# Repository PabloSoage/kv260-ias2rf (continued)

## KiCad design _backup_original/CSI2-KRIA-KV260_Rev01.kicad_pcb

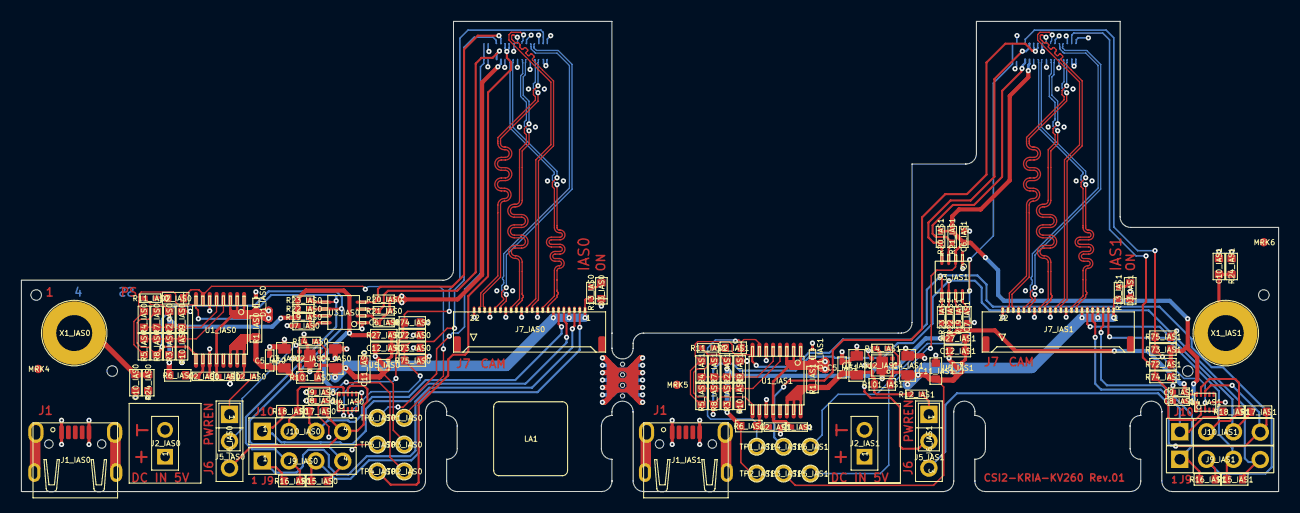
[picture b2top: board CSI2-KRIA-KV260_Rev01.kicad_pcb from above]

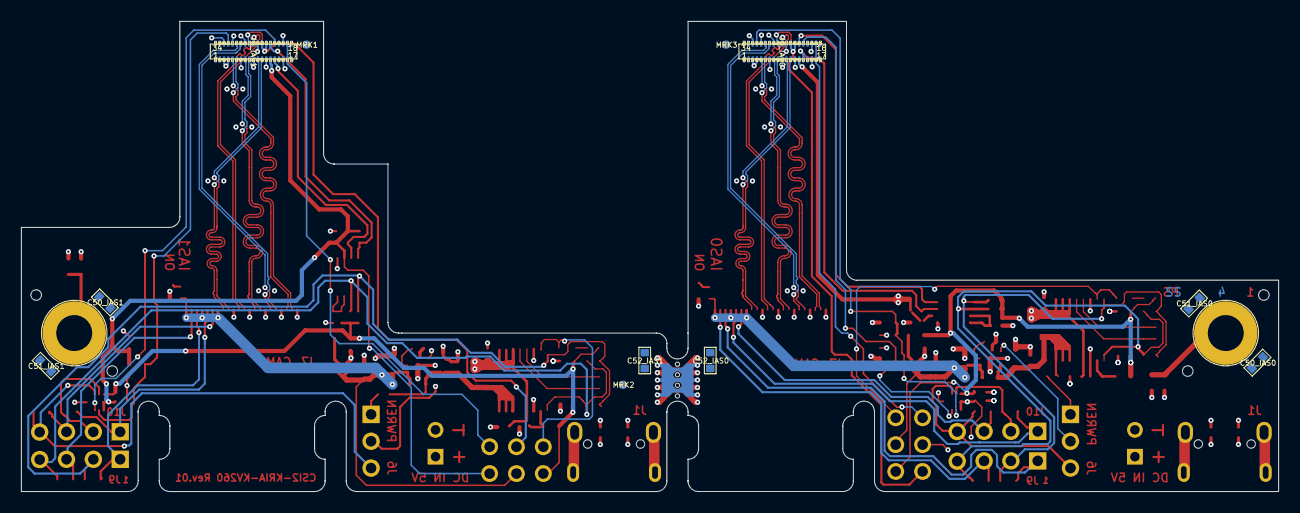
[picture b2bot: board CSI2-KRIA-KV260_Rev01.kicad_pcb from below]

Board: 4 copper layers, 119.0 x 44.5 mm, 145 parts (12 on the bottom side), 82 nets.

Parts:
C1_IAS0, C1_IAS1, C2_IAS0, C2_IAS1: NL; C-0402_0.55
C3_IAS0, C3_IAS1, C4_IAS0, C4_IAS1: 10u; C-0805_1.4
C5_IAS0, C5_IAS1, C6_IAS0, C6_IAS1, C8_IAS0, C8_IAS1, C9_IAS0, C9_IAS1: 100n; C-0402_0.55
C7_IAS0, C7_IAS1: 100p; C-0402_0.55
C10_IAS0, C10_IAS1: NL; C-0603_1.0
C11_IAS0, C11_IAS1, C12_IAS0, C12_IAS1, C50_IAS0, C50_IAS1, C51_IAS0, C51_IAS1, C52_IAS0, C52_IAS1: 4u7; C-0603_1.0
D1_IAS0, D1_IAS1: ESD9B5.0ST5G; D-SOD923
D2_IAS0, D2_IAS1: RED; D-0603-LED
D3_IAS0, D3_IAS1: GREEN; D-0603-LED
J1_IAS0, J1_IAS1: USB 2.0 Typ B 90°; J-629105150521
J2_IAS0, J2_IAS1: CON1x2; CON 1x2 RM2.54
J5_IAS0, J5_IAS1: Jumper; J-JUMPER-2.54
J6_IAS0, J6_IAS1: CON1x3; CON 1x3 RM2.54
J7_IAS0, J7_IAS1: CON FFC22_Inverted; J-FH55-22S-0.5SH - Inverted Pins
J8_IAS0, J8_IAS1: BM20B(0.8)-34DP-0.4V(51); J-BM20B(0.8)-34DP
J9_IAS0, J9_IAS1, J10_IAS0, J10_IAS1: CON1x4; CON 1x4 RM2.54
LA1: LABEL 7x7mm; PCB LABEL 7x7
MRK1, MRK2, MRK3: Marker Single Layer; PCB_Marker_Pad_top
MRK4, MRK5, MRK6: Marker Single Layer; PCB_MARKER_PAD_TOP
R1_IAS0, R1_IAS1, R3_IAS0, R3_IAS1, R9_IAS0, R9_IAS1, R15_IAS0, R15_IAS1, R16_IAS0, R16_IAS1, R24_IAS0, R24_IAS1, R27_IAS0, R27_IAS1: 0R0; R-0603_0.6
R2_IAS0, R2_IAS1, R4_IAS0, R4_IAS1, R5_IAS0, R5_IAS1, R6_IAS0, R6_IAS1, R7_IAS0, R7_IAS1, R8_IAS0, R8_IAS1, R10_IAS0, R10_IAS1, R17_IAS0, R17_IAS1, R18_IAS0, R18_IAS1, R72_IAS0, R72_IAS1, R73_IAS0, R73_IAS1, R74_IAS0, R74_IAS1, R75_IAS0, R75_IAS1, R101_IAS0, R101_IAS1: NL; R-0603_0.6
R11_IAS0, R11_IAS1: NL; R-0402_0.4
R12_IAS0: 270k; R-0402_0.4
R12_IAS1: 270K; R-0402_0.4
R13_IAS0, R13_IAS1: 3k3; R-0402_0.4
R14_IAS0, R14_IAS1: 51k; R-0402_0.4
R19_IAS0, R19_IAS1: 200k; R-0402_0.4
R20_IAS0, R20_IAS1, R21_IAS0, R21_IAS1, R22_IAS0, R22_IAS1, R23_IAS0, R23_IAS1: 2k0; R-0402_0.4
T1: PCB Text TOP; PCB TEXTFIELD TOP 2
T2: PCB Text BOT; PCB TEXTFIELD BOT 2
TP1_IAS0, TP1_IAS1, TP2_IAS0, TP2_IAS1, TP3_IAS0, TP3_IAS1, TP4_IAS0, TP4_IAS1, TP5_IAS0, TP5_IAS1, TP6_IAS0, TP6_IAS1: TP; TP_16_10
U1_IAS0, U1_IAS1: INA260AIPWR; IC-TSSOP16 6.4x5.1x1.2
U2_IAS0, U2_IAS1: TPS25200DRVT; IC-DFN06_2.0x2.0x0.8
U3_IAS0, U3_IAS1: PCA9306DCTR; IC-TSSOP8_3.15x4.25x1.3
U4_IAS0, U4_IAS1: NTB0104GU12,115; IC-XQFN12_1.7x2x0.5
U5_IAS0, U5_IAS1: NCP114AMX330TCG; IC-XDFN4_1.0x1.0x0.6
X1_IAS0, X1_IAS1: Hole; HOLE-3.4-6.0-DK

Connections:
B7-CSI2-TXC_IAS0_N: J7_IAS0.14, J8_IAS0.8
B7-CSI2-TXC_IAS0_P: J7_IAS0.15, J8_IAS0.7
B7-CSI2-TXC_IAS1_N: J7_IAS1.14, J8_IAS1.8
B7-CSI2-TXC_IAS1_P: J7_IAS1.15, J8_IAS1.7
B7-CSI2-TXD0_IAS0_N: J7_IAS0.20, J8_IAS0.5
B7-CSI2-TXD0_IAS0_P: J7_IAS0.21, J8_IAS0.4
B7-CSI2-TXD0_IAS1_N: J7_IAS1.20, J8_IAS1.5
B7-CSI2-TXD0_IAS1_P: J7_IAS1.21, J8_IAS1.4
B7-CSI2-TXD1_IAS0_N: J7_IAS0.17, J8_IAS0.29
B7-CSI2-TXD1_IAS0_P: J7_IAS0.18, J8_IAS0.30
B7-CSI2-TXD1_IAS1_N: J7_IAS1.17, J8_IAS1.29
B7-CSI2-TXD1_IAS1_P: J7_IAS1.18, J8_IAS1.30
B7-CSI2-TXD2_IAS0_N: J7_IAS0.11, J8_IAS0.26
B7-CSI2-TXD2_IAS0_P: J7_IAS0.12, J8_IAS0.27
B7-CSI2-TXD2_IAS1_N: J7_IAS1.11, J8_IAS1.26
B7-CSI2-TXD2_IAS1_P: J7_IAS1.12, J8_IAS1.27
B7-CSI2-TXD3_IAS0_N: J7_IAS0.8, J8_IAS0.11
B7-CSI2-TXD3_IAS0_P: J7_IAS0.9, J8_IAS0.10
B7-CSI2-TXD3_IAS1_N: J7_IAS1.8, J8_IAS1.11
B7-CSI2-TXD3_IAS1_P: J7_IAS1.9, J8_IAS1.10
C-GND_IAS0: C10_IAS0.2, J1_IAS0.6, J1_IAS0.7, J1_IAS0.8, J1_IAS0.9, R24_IAS0.1, X1_IAS0.1
C-GND_IAS1: C10_IAS1.2, J1_IAS1.6, J1_IAS1.7, J1_IAS1.8, J1_IAS1.9, R24_IAS1.1, X1_IAS1.1
EXT-GPIO0-I2C-SCL_IAS0: J7_IAS0.2, J9_IAS0.3, R15_IAS0.1
EXT-GPIO0-I2C-SCL_IAS1: J7_IAS1.2, J9_IAS1.3, R15_IAS1.1
EXT-GPIO1-I2C-SDA_IAS0: J7_IAS0.3, J9_IAS0.1, R16_IAS0.1
EXT-GPIO1-I2C-SDA_IAS1: J7_IAS1.3, J9_IAS1.1, R16_IAS1.1
EXT-GPIO2_IAS0: J7_IAS0.5, J10_IAS0.1, R18_IAS0.1
EXT-GPIO2_IAS1: J7_IAS1.5, J10_IAS1.1, R18_IAS1.1
EXT-GPIO3_IAS0: J7_IAS0.6, J10_IAS0.3, R17_IAS0.1
EXT-GPIO3_IAS1: J7_IAS1.6, J10_IAS1.3, R17_IAS1.1
GND: C1_IAS0.2, C1_IAS1.2, C2_IAS0.2, C2_IAS1.2, C3_IAS0.2, C3_IAS1.2, C4_IAS0.2, C4_IAS1.2, C5_IAS0.2, C5_IAS1.2, C6_IAS0.2, C6_IAS1.2, C7_IAS0.2, C7_IAS1.2, C8_IAS0.2, C8_IAS1.2, C9_IAS0.2, C9_IAS1.2, C10_IAS0.1, C10_IAS1.1, C11_IAS0.2, C11_IAS1.2, C12_IAS0.2, C12_IAS1.2, D1_IAS0.A, D1_IAS1.A, D3_IAS0.K, D3_IAS1.K, J1_IAS0.5, J1_IAS1.5, J2_IAS0.2, J2_IAS1.2, J7_IAS0.10, J7_IAS0.13, J7_IAS0.16, J7_IAS0.19, J7_IAS0.22, J7_IAS1.10, J7_IAS1.13, J7_IAS1.16, J7_IAS1.19, J7_IAS1.22, J8_IAS0.2, J8_IAS0.3, J8_IAS0.6, J8_IAS0.9, J8_IAS0.12, J8_IAS0.16, J8_IAS0.19, J8_IAS0.25, J8_IAS0.28, J8_IAS0.31, J8_IAS0.33, J8_IAS1.2, J8_IAS1.3, J8_IAS1.6, J8_IAS1.9, J8_IAS1.12, J8_IAS1.16, J8_IAS1.19, J8_IAS1.25, J8_IAS1.28, J8_IAS1.31, J8_IAS1.33, R9_IAS0.1, R9_IAS1.1, R10_IAS0.1, R10_IAS1.1, R14_IAS0.1, R14_IAS1.1, R24_IAS0.2, R24_IAS1.2, R74_IAS0.1, R74_IAS1.1, R75_IAS0.1, R75_IAS1.1, U1_IAS0.6, U1_IAS0.11, U1_IAS1.6, U1_IAS1.11, U2_IAS0.5, U2_IAS0.7, U2_IAS1.5, U2_IAS1.7, U3_IAS0.1, U3_IAS1.1, U4_IAS0.6, U4_IAS1.6, U5_IAS0.2, U5_IAS0.5, U5_IAS1.2, U5_IAS1.5
GPIO2_3V3_IAS0: J10_IAS0.2, R18_IAS0.2, U4_IAS0.10
GPIO2_3V3_IAS1: J10_IAS1.2, R18_IAS1.2, U4_IAS1.10
GPIO2_IAS0: J8_IAS0.32, R72_IAS0.1, R74_IAS0.2, U4_IAS0.2
GPIO2_IAS1: J8_IAS1.32, R72_IAS1.1, R74_IAS1.2, U4_IAS1.2
GPIO3_3V3_IAS0: J6_IAS0.3, J10_IAS0.4, R17_IAS0.2, U4_IAS0.9
GPIO3_3V3_IAS1: J6_IAS1.3, J10_IAS1.4, R17_IAS1.2, U4_IAS1.9
I2C_SCL_3V3_IAS0: J9_IAS0.4, R7_IAS0.1, R8_IAS0.1, R15_IAS0.2, R22_IAS0.1, U1_IAS0.9, U3_IAS0.6
I2C_SCL_3V3_IAS1: J9_IAS1.4, R7_IAS1.1, R8_IAS1.1, R15_IAS1.2, R22_IAS1.1, U1_IAS1.9, U3_IAS1.6
I2C_SCL_IAS0: J8_IAS0.14, R21_IAS0.2, U3_IAS0.3
I2C_SCL_IAS1: J8_IAS1.14, R21_IAS1.2, U3_IAS1.3
I2C_SDA_3V3_IAS0: J9_IAS0.2, R4_IAS0.1, R5_IAS0.1, R16_IAS0.2, R23_IAS0.1, U1_IAS0.8, U3_IAS0.5
I2C_SDA_3V3_IAS1: J9_IAS1.2, R4_IAS1.1, R5_IAS1.1, R16_IAS1.2, R23_IAS1.1, U1_IAS1.8, U3_IAS1.5
I2C_SDA_IAS0: J8_IAS0.22, R20_IAS0.2, U3_IAS0.4
I2C_SDA_IAS1: J8_IAS1.22, R20_IAS1.2, U3_IAS1.4
INA260-A0_IAS0: R2_IAS0.2, R4_IAS0.2, R7_IAS0.2, R9_IAS0.2, U1_IAS0.5
INA260-A0_IAS1: R2_IAS1.2, R4_IAS1.2, R7_IAS1.2, R9_IAS1.2, U1_IAS1.5
INA260-A1_IAS0: R3_IAS0.2, R5_IAS0.2, R8_IAS0.2, R10_IAS0.2, U1_IAS0.4
INA260-A1_IAS1: R3_IAS1.2, R5_IAS1.2, R8_IAS1.2, R10_IAS1.2, U1_IAS1.4
NetC2_IAS0_1: C2_IAS0.1, R6_IAS0.2, U1_IAS0.10
NetC2_IAS1_1: C2_IAS1.1, R6_IAS1.2, U1_IAS1.10
NetC7_IAS0_1: C7_IAS0.1, R19_IAS0.1, U3_IAS0.7, U3_IAS0.8
NetC7_IAS1_1: C7_IAS1.1, R19_IAS1.1, U3_IAS1.7, U3_IAS1.8
NetC12_IAS0_1: C12_IAS0.1, R27_IAS0.1, U5_IAS0.1
NetC12_IAS1_1: C12_IAS1.1, R27_IAS1.1, U5_IAS1.1
NetD2_IAS0_A: D2_IAS0.A, R11_IAS0.2
NetD2_IAS0_K: D2_IAS0.K, TP1_IAS0.1, U1_IAS0.7
NetD2_IAS1_A: D2_IAS1.A, R11_IAS1.2
NetD2_IAS1_K: D2_IAS1.K, TP1_IAS1.1, U1_IAS1.7
NetD3_IAS0_A: D3_IAS0.A, R13_IAS0.2
NetD3_IAS1_A: D3_IAS1.A, R13_IAS1.2
NetJ6_IAS0_1: J6_IAS0.1, R12_IAS0.2
NetJ6_IAS0_2: J6_IAS0.2, U2_IAS0.4
NetJ6_IAS1_1: J6_IAS1.1, R12_IAS1.2
NetJ6_IAS1_2: J6_IAS1.2, U2_IAS1.4
NetR14_IAS0_2: R14_IAS0.2, U2_IAS0.2
NetR14_IAS1_2: R14_IAS1.2, U2_IAS1.2
PWDN_IAS0: J8_IAS0.21, R73_IAS0.1, R75_IAS0.2, U4_IAS0.3
PWDN_IAS1: J8_IAS1.21, R73_IAS1.1, R75_IAS1.2, U4_IAS1.3
VCC1V2_IAS0: J8_IAS0.23, J8_IAS0.24, TP4_IAS0.1
VCC1V2_IAS1: J8_IAS1.23, J8_IAS1.24, TP4_IAS1.1
VCC1V8_IAS0: C6_IAS0.1, C8_IAS0.1, J8_IAS0.13, R20_IAS0.1, R21_IAS0.1, R72_IAS0.2, R73_IAS0.2, TP5_IAS0.1, U3_IAS0.2, U4_IAS0.1, U4_IAS0.12
VCC1V8_IAS1: C6_IAS1.1, C8_IAS1.1, J8_IAS1.13, R20_IAS1.1, R21_IAS1.1, R72_IAS1.2, R73_IAS1.2, TP5_IAS1.1, U3_IAS1.2, U4_IAS1.1, U4_IAS1.12
VCC2V75_IAS0: J8_IAS0.17, J8_IAS0.18, TP6_IAS0.1
VCC2V75_IAS1: J8_IAS1.17, J8_IAS1.18, TP6_IAS1.1
VCC3V3_IAS0: C9_IAS0.1, R2_IAS0.1, R3_IAS0.1, R6_IAS0.1, R11_IAS0.1, R19_IAS0.2, R22_IAS0.2, R23_IAS0.2, R27_IAS0.2, TP2_IAS0.1, U4_IAS0.11
VCC3V3_IAS1: C9_IAS1.1, R2_IAS1.1, R3_IAS1.1, R6_IAS1.1, R11_IAS1.1, R19_IAS1.2, R22_IAS1.2, R23_IAS1.2, R27_IAS1.2, TP2_IAS1.1, U4_IAS1.11
VCC5V-CAM_IAS0: C3_IAS0.1, C5_IAS0.1, R1_IAS0.1, R12_IAS0.1, R101_IAS0.2, U1_IAS0.14, U1_IAS0.15, U1_IAS0.16, U2_IAS0.6
VCC5V-CAM_IAS1: C3_IAS1.1, C5_IAS1.1, R1_IAS1.1, R12_IAS1.1, R101_IAS1.2, U1_IAS1.14, U1_IAS1.15, U1_IAS1.16, U2_IAS1.6
VCC5V-EXT: C1_IAS0.1, C1_IAS1.1, D1_IAS0.K, D1_IAS1.K, J1_IAS0.1, J1_IAS1.1, J2_IAS0.1, J2_IAS1.1, R1_IAS0.2, R1_IAS1.2, U1_IAS0.1, U1_IAS0.2, U1_IAS0.3, U1_IAS0.12, U1_IAS1.1, U1_IAS1.2, U1_IAS1.3, U1_IAS1.12
VCC-EXT-IN_IAS0: C4_IAS0.1, C11_IAS0.1, J7_IAS0.1, J7_IAS0.4, J7_IAS0.7, R13_IAS0.1, R101_IAS0.1, TP3_IAS0.1, U2_IAS0.1, U5_IAS0.3, U5_IAS0.4
VCC-EXT-IN_IAS1: C4_IAS1.1, C11_IAS1.1, J7_IAS1.1, J7_IAS1.4, J7_IAS1.7, R13_IAS1.1, R101_IAS1.1, TP3_IAS1.1, U2_IAS1.1, U5_IAS1.3, U5_IAS1.4
